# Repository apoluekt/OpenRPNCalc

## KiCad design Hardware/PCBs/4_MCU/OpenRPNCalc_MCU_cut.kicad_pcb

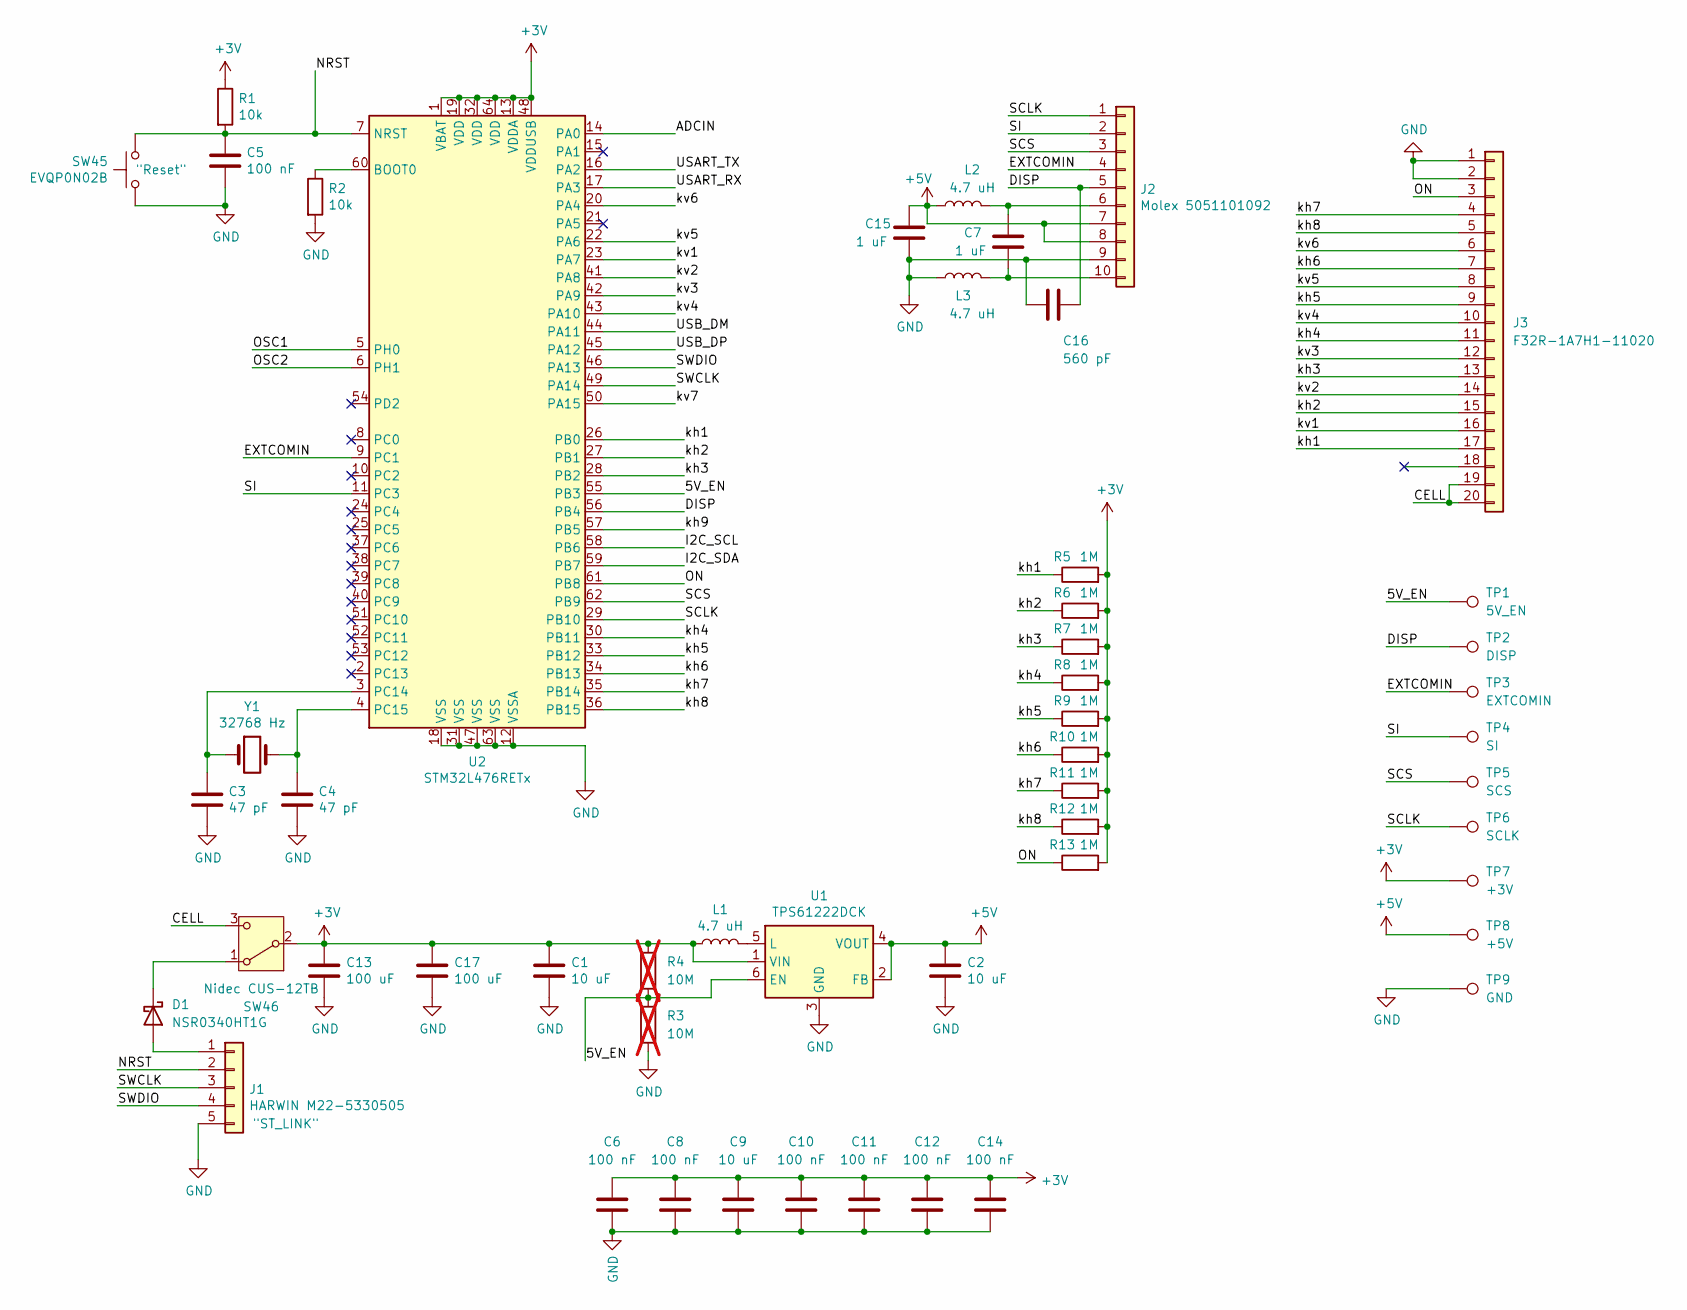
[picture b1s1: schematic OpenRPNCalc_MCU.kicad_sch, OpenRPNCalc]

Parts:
C1, C2, C9: 10 uF; C_0603_1608Metric_Pad1.08x0.95mm_HandSolder
C3, C4: 47 pF; C_0603_1608Metric_Pad1.08x0.95mm_HandSolder
C5, C6, C8, C10, C11, C12, C14: 100 nF; C_0603_1608Metric_Pad1.08x0.95mm_HandSolder
C7, C15: 1 uF; C_0603_1608Metric_Pad1.08x0.95mm_HandSolder
C13, C17: 100 uF; C_1206_3216Metric_Pad1.33x1.80mm_HandSolder
C16: 560 pF; C_0603_1608Metric_Pad1.08x0.95mm_HandSolder
D1: NSR0340HT1G; D_SOD-323_HandSoldering
J1: HARWIN M22-5330505; HARWIN_M22-5330505
J2: Molex 5051101092; CON_5051101092_MOL
J3: F32R-1A7H1-11020; AMPHENOL_F32R-1A7H1-11020
L1, L2, L3: 4.7 uH; L_0805_2012Metric_Pad1.15x1.40mm_HandSolder
R1, R2: 10k; R_0603_1608Metric_Pad0.98x0.95mm_HandSolder
R3, R4: 10M; R_0603_1608Metric_Pad0.98x0.95mm_HandSolder; not fitted
R5, R6, R7, R8, R9, R10, R11, R12, R13: 1M; R_0603_1608Metric_Pad0.98x0.95mm_HandSolder
SW45: EVQP0N02B; SW_SPST_EVQQ2
SW46: Nidec CUS-12TB; CUS-12TB_NDC
TP1: 5V_EN; TestPoint_Pad_D2.0mm
TP2: DISP; TestPoint_Pad_D2.0mm
TP3: EXTCOMIN; TestPoint_Pad_D2.0mm
TP4: SI; TestPoint_Pad_D2.0mm
TP5: SCS; TestPoint_Pad_D2.0mm
TP6: SCLK; TestPoint_Pad_D2.0mm
TP7: +3V; TestPoint_Pad_D2.0mm
TP8: +5V; TestPoint_Pad_D2.0mm
TP9: GND; TestPoint_Pad_D2.0mm
U1: TPS61222DCK; Texas_R-PDSO-G6
U2: STM32L476RETx; LQFP-64_10x10mm_P0.5mm
Y1: 32768 Hz; Crystal_SMD_2012-2Pin_2.0x1.2mm_HandSoldering

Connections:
+5V: C2.1, C15.1, J2.7, J2.8, L2.1, TP8.1, U1.2 (FB), U1.4 (VOUT)
+BATT: C1.1, C6.2, C8.2, C9.2, C10.2, C11.2, C12.2, C13.1, C14.2, C17.1, L1.1, R1.1, R4.1, R5.2, R6.2, R7.2, R8.2, R9.2, R10.2, R11.2, R12.2, R13.2, SW46.2 (B), TP7.1, U1.1 (VIN), U2.1 (VBAT), U2.13 (VDDA), U2.19 (VDD), U2.32 (VDD), U2.48 (VDDUSB), U2.64 (VDD)
/5V_EN: R3.1, R4.2, TP1.1, U1.6 (EN), U2.55 (PB3)
/ADCIN: U2.14 (PA0)
/CELL: J3.19, J3.20, SW46.3 (C)
/DISP: C16.1, J2.5, TP2.1, U2.56 (PB4)
/EXTCOMIN: J2.4, TP3.1, U2.9 (PC1)
/I2C_SCL: U2.58 (PB6)
/I2C_SDA: U2.59 (PB7)
/NRST: C5.1, J1.2, R1.2, SW45.1, U2.7 (NRST)
/ON: J3.3, R13.1, U2.61 (PB8)
/OSC1: U2.5 (PH0)
/OSC2: U2.6 (PH1)
/SCLK: J2.1, TP6.1, U2.29 (PB10)
/SCS: J2.3, TP5.1, U2.62 (PB9)
/SI: J2.2, TP4.1, U2.11 (PC3)
/SWCLK: J1.3, U2.49 (PA14)
/SWDIO: J1.4, U2.46 (PA13)
/USART_RX: U2.17 (PA3)
/USART_TX: U2.16 (PA2)
/USB_DM: U2.44 (PA11)
/USB_DP: U2.45 (PA12)
/kh1: J3.17, R5.1, U2.26 (PB0)
/kh2: J3.15, R6.1, U2.27 (PB1)
/kh3: J3.13, R7.1, U2.28 (PB2)
/kh4: J3.11, R8.1, U2.30 (PB11)
/kh5: J3.9, R9.1, U2.33 (PB12)
/kh6: J3.7, R10.1, U2.34 (PB13)
/kh7: J3.4, R11.1, U2.35 (PB14)
/kh8: J3.5, R12.1, U2.36 (PB15)
/kh9: U2.57 (PB5)
/kv1: J3.16, U2.23 (PA7)
/kv2: J3.14, U2.41 (PA8)
/kv3: J3.12, U2.42 (PA9)
/kv4: J3.10, U2.43 (PA10)
/kv5: J3.8, U2.22 (PA6)
/kv6: J3.6, U2.20 (PA4)
/kv7: U2.50 (PA15)
GND: C1.2, C2.2, C3.2, C4.2, C5.2, C6.1, C8.1, C9.1, C10.1, C11.1, C12.1, C13.2, C14.1, C15.2, C16.2, C17.2, J1.5, J2.9, J3.1, J3.2, L3.1, R2.2, R3.2, SW45.2, TP9.1, U1.3 (GND), U2.12 (VSSA), U2.18 (VSS), U2.31 (VSS), U2.47 (VSS), U2.63 (VSS)
unnamed: D1.2 (A), J1.1
unnamed: D1.1 (K), SW46.1 (A)
unnamed: C7.1, J2.6, L2.2
unnamed: C7.2, J2.10, L3.2
unnamed: L1.2, U1.5 (L)
unnamed: R2.1, U2.60 (BOOT0)
unnamed: C3.1, U2.3 (PC14), Y1.1
unnamed: C4.1, U2.4 (PC15), Y1.2

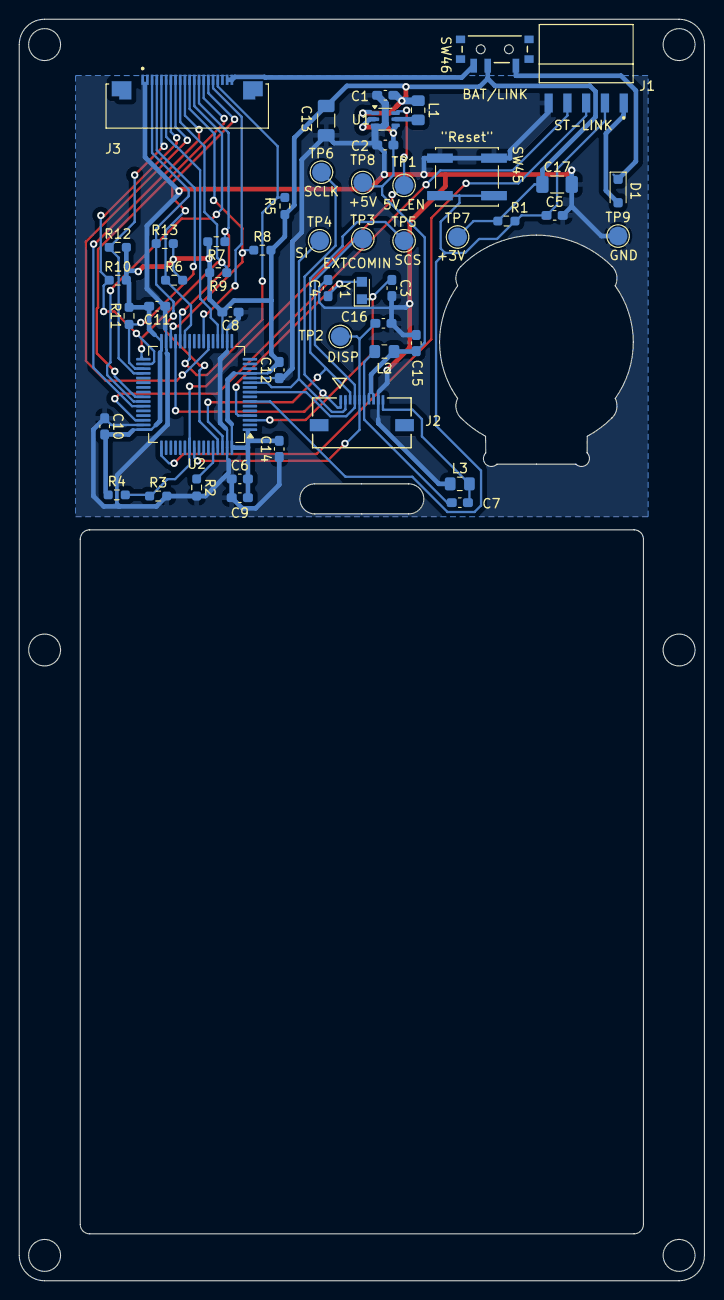
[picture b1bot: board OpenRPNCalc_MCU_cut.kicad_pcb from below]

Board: 2 copper layers, 73.0 x 134.4 mm, 51 parts (51 on the bottom side), 36 nets.
